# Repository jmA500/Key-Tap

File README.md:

# Key-Tap

This little gadget can listen to the keyboard of an Amiga 500 and catch
certain hotkeys. These hotkeys can be used to drive output pins that can 
configure internal extentions. 

Please have a look at the project website:

https://www.jm27.de/key-tap-a-hardware-configurator-for-the-amiga-500/

# License

	All material is freely usable under the GPL v2

# Directory structure

	* hardware: Contains Eagle PCB files
	* firmware: Pre-built hex-files for different MCUs
	* src: the C-source code
	* doc: Documentation

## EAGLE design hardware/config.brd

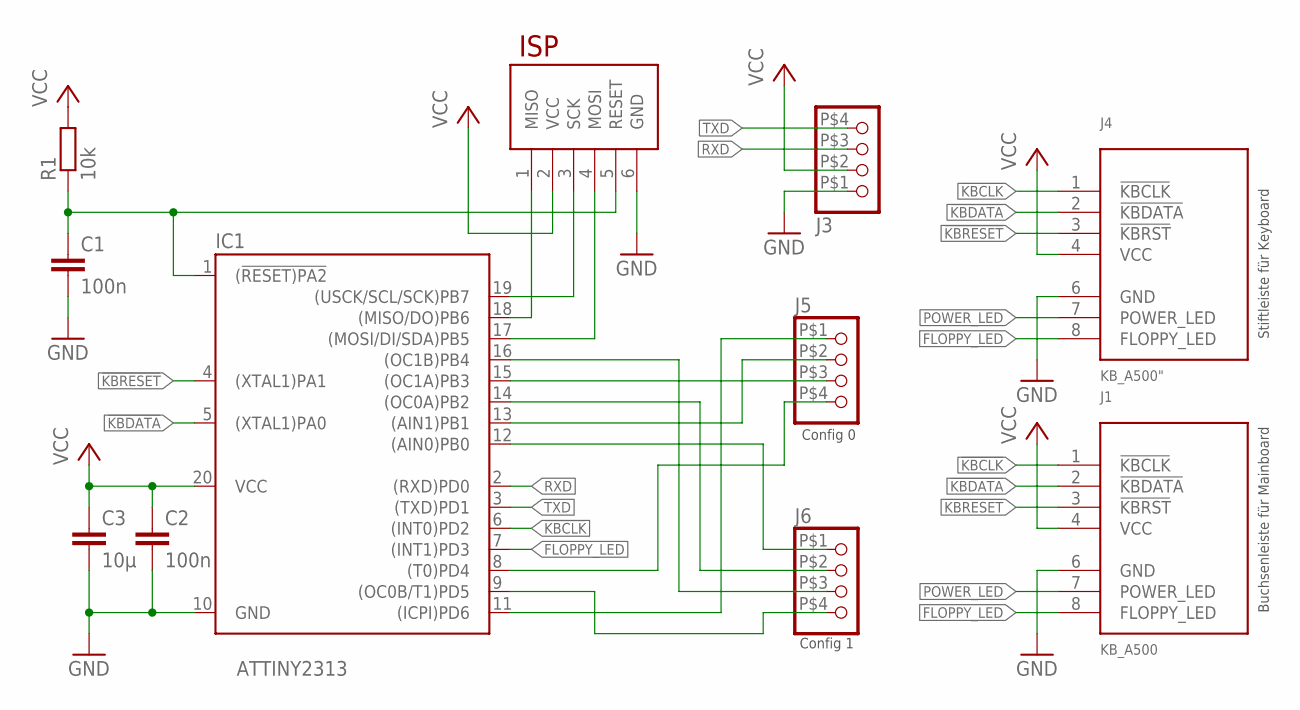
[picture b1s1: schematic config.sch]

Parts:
C1, C2: 100n; C0805
C3: 10µ; C1206
IC1: ATTINY2313; SO20L
J1: KB_A500; 1X08S
J2: ISP; 2X03
J3, J5, J6: PINHD-1X4; 1X04SLIM
J4: KB_A500"; 1X08/90SLIM
R1: 10k; R0805

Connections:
!KBCLK: IC1.6 ((INT0)PD2), J1.1 (!KBCLK), J4.1 (!KBCLK)
!KBDATA: IC1.5 ((XTAL1)PA0), J1.2 (!KBDATA), J4.2 (!KBDATA)
!KBRESET: IC1.4 ((XTAL1)PA1), J1.3 (!KBRST), J4.3 (!KBRST)
FLOPPY_LED: IC1.7 ((INT1)PD3), J1.8 (FLOPPY_LED), J4.8 (FLOPPY_LED)
GND: C1.2, C2.2, C3.2, IC1.10 (GND), J1.6 (GND), J2.6 (GND), J3.P$1 (1), J4.6 (GND)
MISO: IC1.18 ((MISO/DO)PB6), J2.1 (MISO)
MOSI: IC1.17 ((MOSI/DI/SDA)PB5), J2.4 (MOSI)
unnamed: IC1.12 ((AIN0)PB0), J6.P$1 (1)
unnamed: IC1.9 ((OC0B/T1)PD5), J6.P$4 (4)
unnamed: C1.1, IC1.1 ((!RESET)PA2), J2.5 (RESET), R1.1
PB1: IC1.13 ((AIN1)PB1), J5.P$2 (2)
PB2: IC1.14 ((OC0A)PB2), J6.P$2 (2)
PB3: IC1.15 ((OC1A)PB3), J5.P$3 (3)
PB4: IC1.16 ((OC1B)PB4), J6.P$3 (3)
PD4: IC1.8 ((T0)PD4), J5.P$4 (4)
PD6: IC1.11 ((ICPI)PD6), J5.P$1 (1)
POWER_LED: J1.7 (POWER_LED), J4.7 (POWER_LED)
RXD: IC1.2 ((RXD)PD0), J3.P$3 (3)
SCK: IC1.19 ((USCK/SCL/SCK)PB7), J2.3 (SCK)
TXD: IC1.3 ((TXD)PD1), J3.P$4 (4)
VCC: C2.1, C3.1, IC1.20 (VCC), J1.4 (VCC), J2.2 (VCC), J3.P$2 (2), J4.4 (VCC), R1.2

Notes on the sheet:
Config 0
Config 1
Buchsenleiste für Mainboard
Stiftleiste für Keyboard

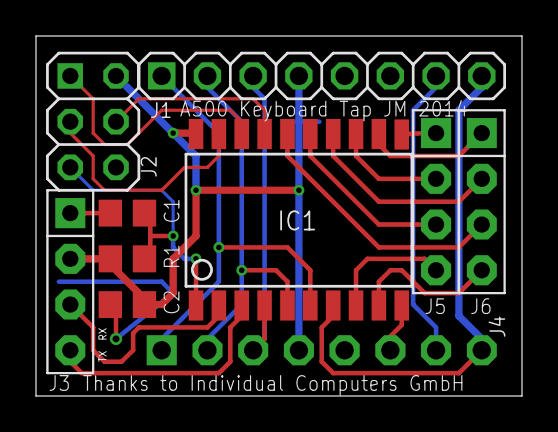
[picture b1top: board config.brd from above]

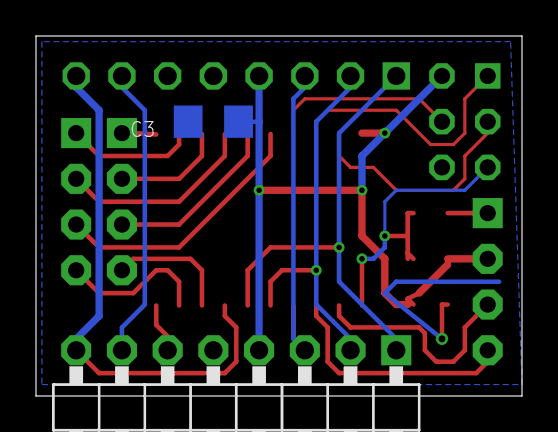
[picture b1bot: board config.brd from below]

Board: 2 copper layers, 27.0 x 20.0 mm, 11 parts (2 on the bottom side), 21 nets.

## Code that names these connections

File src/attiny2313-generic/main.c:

/************************************************************************
Title:    Main file for the firmware of an Amiga 500 Configurator. 
          Listens to the keyboard and takes keypresses to configure the 
          Amiga via some pins of the MCU.

Author:   Jan Metzger <jm@metweb.de>

License:  GNU General Public License 

LICENSE:
    Copyright (C) 2014-2017 Jan Metzger

    This program is free software; you can redistribute it and/or modify
    it under the terms of the GNU General Public License as published by
    the Free Software Foundation; either version 2 of the License, or
    any later version.

    This program is distributed in the hope that it will be useful,
    but WITHOUT ANY WARRANTY; without even the implied warranty of
    MERCHANTABILITY or FITNESS FOR A PARTICULAR PURPOSE.  See the
    GNU General Public License for more details.
    
************************************************************************/

#include <avr/io.h>
#include <avr/interrupt.h>
#include <avr/pgmspace.h>
#include <avr/eeprom.h>
#include <stdint.h>
#include <stdio.h>
#include <string.h>
#include <util/delay.h>
#include <ctype.h>
#include "key_tap.h"
#include "util.h"
#include "uart.h"
#include "uart_helper.h"
#include "ee_helper.h"

#define UART_DEBUG

#define CONFIG_PORT0 PORTD
#define CONFIG_DDR0  DDRD
#define CONFIG_BIT0  PD6

#define CONFIG_PORT1 PORTB
#define CONFIG_DDR1  DDRB
#define CONFIG_BIT1  PB1
 
#define CONFIG_PORT2 PORTB
#define CONFIG_DDR2  DDRB
#define CONFIG_BIT2  PB3 

#define CONFIG_PORT3 PORTD
#define CONFIG_DDR3  DDRD
#define CONFIG_BIT3  PD4 

#define CONFIG_PORT4 PORTB
#define CONFIG_DDR4  DDRB
#define CONFIG_BIT4  PB0
 
#define CONFIG_PORT5 PORTB
#define CONFIG_DDR5  DDRB
#define CONFIG_BIT5  PB2 
 
#define CONFIG_PORT6 PORTB
#define CONFIG_DDR6  DDRB
#define CONFIG_BIT6  PB4

#define CONFIG_PORT7 PORTD
#define CONFIG_DDR7  DDRD
#define CONFIG_BIT7  PD5

#define SET_BIT_TRI(PORT,DDR,BIT,STATE) { \
    if (STATE) \
      { (PORT) &= ~(1<<(BIT)); (DDR) |= (1<<(BIT)); } \
    else \
      { (DDR) &= ~(1<<(BIT)); } }

/* 
   The following variables store the current config. 
   Every bit corresponds to a config pin.
   Note that the interpretation is 'negative logic':
     1 means that the pin is pulled low (i.e. jumper on)
     0 means that the pin is high-z (i.e. jumper off)
*/

static struct
{
  uint8_t current;
  uint8_t next;
} conf;

void set_config()
{
  ee_save_config(conf.next);
  conf.current = conf.next;
  SET_BIT_TRI(CONFIG_PORT0, CONFIG_DDR0, CONFIG_BIT0, conf.current & (1<<0));
  SET_BIT_TRI(CONFIG_PORT1, CONFIG_DDR1, CONFIG_BIT1, conf.current & (1<<1));
  SET_BIT_TRI(CONFIG_PORT2, CONFIG_DDR2, CONFIG_BIT2, conf.current & (1<<2));
  SET_BIT_TRI(CONFIG_PORT3, CONFIG_DDR3, CONFIG_BIT3, conf.current & (1<<3));
  SET_BIT_TRI(CONFIG_PORT4, CONFIG_DDR4, CONFIG_BIT4, conf.current & (1<<4));
  SET_BIT_TRI(CONFIG_PORT5, CONFIG_DDR5, CONFIG_BIT5, conf.current & (1<<5));
  SET_BIT_TRI(CONFIG_PORT6, CONFIG_DDR6, CONFIG_BIT6, conf.current & (1<<6));
  SET_BIT_TRI(CONFIG_PORT7, CONFIG_DDR7, CONFIG_BIT7, conf.current & (1<<7));

#ifdef UART_DEBUG  
  while (uart_tx_char_present());
  uart_puts_P("CFG Load");
  uart_put_hex(conf.current);
  uart_put_newline();
#endif

  delay_ms(500);
}

inline void init()
{
  sei();
#ifdef UART_DEBUG  
  uart_init();
  uart_puts_P("KEYTAP Generic v1.0 JM 2017\n");
#endif
  kbd_init();
}

void uart_print_next()
{
#ifdef UART_DEBUG
  while (uart_tx_char_present());
  uart_puts_P("CFG next");
  uart_put_hex(conf.next);
  uart_put_newline();
#endif
}

void uart_print_current()
{
#ifdef UART_DEBUG
  while (uart_tx_char_present());
  uart_puts_P("CFG now");
  uart_put_hex(conf.current);
  uart_put_newline();
#endif
}

inline void uart_print_help()
{
#ifdef UART_DEBUG
  while (uart_tx_char_present());
  uart_puts_P("Commands\n?: Show\nh: help\n");
  while (uart_tx_char_present());
  uart_puts_P("! xx : Set config to hex value xx \n");
  while (uart_tx_char_present());
  uart_puts_P("res: reset\n");
#endif
}

inline void uart_print_err()
{
#ifdef UART_DEBUG
  while (uart_tx_char_present());
  uart_puts_P("Error\n");
#endif
}

inline void uart_print_fkey(uint8_t lastfkey)
{
#ifdef UART_DEBUG
  while (uart_tx_char_present());
  uart_puts_P("KEY reg F");
  uart_put_hex(lastfkey);
  uart_put_newline();
#endif
}

/* Parse input from UART. Format is simple but rigid, see uart_print_help() */
void parse (char* str)
{
  switch (str[0])
    {
    case '?':
      uart_print_next();
      uart_print_current();
      break;
    case 'h':
      uart_print_help();
      break;
    case '!':
      {
	uint8_t pos = 1;
	uint8_t resa,resb;

	while (str[pos]==' ')
	  { pos++; }

	resa = hexctoi(str[pos]);
	if (resa != 255)
	  {
	    resb = hexctoi(str[pos+1]);
	    if (resb != 255)
	      {
		conf.next = (resa<<4) + resb;
		uart_print_next();
	      }
	    else
	      {
		uart_print_err();
	      }
	  }
	else
	  {
	    uart_print_err();
	  }
      }
      break;
    case 'r':
      if ((str[1] == 'e') && (str[2] == 's'))
	{
	  kbd_do_reset();
	  set_config();
	  kbd_do_reset();
	}
      break;
    }
}

#define UARTBUF 16
void check_uart()
{
#ifdef UART_DEBUG
  static char buf[UARTBUF];
  static uint8_t bufpos = 0;

  if (uart_rx_char_present())
    {
      char res = uart_getc();
      switch (res)
	{
	case '\r':
	case '\n':
	  buf[bufpos] = 0;
	  parse(buf);
	  bufpos = 0;
	  break;
	case '\b':
	  if (bufpos)
	    bufpos--;
	  break;
	default:
	  if (bufpos < UARTBUF - 1)
	    {
	      buf[bufpos] = res;
	      bufpos++;
	    }
	}
    }
#endif 
}

int __attribute__((OS_main))
main()
{
  init();
  conf.next = ee_load_config();
  set_config();

  uint8_t res;
  uint8_t lastfkey = 0;
  uint8_t help_cnt = 0;
  uint8_t del_cnt = 0;
  uint8_t shift_flag = 0;

  for (;;)
    {
      check_uart();

      if (kbd_get_key(&res))
	{
	  /* The keycode is in the upper seven bits, push/release in the LSB, 
	     LSB = 0 if key is pressed, LSB = 1 if released*/
	  uint8_t code = res >> 1;
	  uint8_t push = (~res & 0x01);

	  /* This is the code that decides what to do if a keypress is detected.
	     Note that it also keeps track whether shift is active or not */
	  if (push)
	    {
	      if (code == KEY_HELP)
		{
		  help_cnt++;
		  if (help_cnt == 3)
		    {
		      if (lastfkey)
			{
			  uint8_t next = conf.next;
			  if ( (0 < lastfkey) && (lastfkey <= 8) )
			    {
			      next |= (1 << (lastfkey-1));
			    }
			  else if ( (11 <= lastfkey) && (lastfkey <= 18))
			    {
			      next &= ~(1 << (lastfkey - 11));
			    }
			  conf.next = next;
			  uart_print_next();
			}
		      else
			{
			  uart_puts_P("CFG no F before help\n");
			}
		    }
		}
	      else
		{
		  help_cnt = 0;
		  lastfkey = 0;
		}

	      if (code == KEY_DELETE)
		{
		  del_cnt++;
		  if (del_cnt == 3)
		    {
		      uart_print_current();
		      uart_print_next();
		    }
		}
	      else
		{
		  del_cnt = 0;
		}

	      if ((KEY_F1 <= code) & (code <= KEY_F10))
		{
		  lastfkey = code - KEY_F1 +1;
		  if (shift_flag)
		    lastfkey += 10;
		  uart_print_fkey(lastfkey);
		}

	      if ((code == KEY_SHIFTL) || (code == KEY_SHIFTR))
		{
		  shift_flag = 1;
		}
	    }
	  else
	    {
	      if ((code == KEY_SHIFTL) || (code==KEY_SHIFTR))
		{
		  shift_flag = 0;
		}
	    }
	}

      if (kbd_got_reset())
      	{
      	  set_config();
      	}
      
      if (kbd_got_long_reset())
	{
	  conf.next = CONFIG_DEFAULT;
      	  set_config();
	}
    }

  return 0;
}

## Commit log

2021-03-13 Initil import
2021-03-13 Typo corrected
2021-03-25 * Added a new function to the generic version:
    To configure an RGBtoHDMI Adapter one needs to emulate short and long
    pushes to a push button. This is done on the last Config Pin (JP6 / pin 4)
    when Pushing F9 (short) or F10 (long) while Holding HELP.
    Caveat: UART debugging is untested
2021-03-25 Added firmware files.
2021-03-25 * Added new PCB version with Atmega88
2021-03-25 * Removed an old testing version of the source code * Source for new Atmega88 version will be added later
2021-03-26 * Added two solder Jumpers for Hardware configurability * Increased length of PCB tomake it sit on the DSUb connector in the back of an A500
2021-03-29 * Makefile: Deleted -y Flag for avrdude * main.c: Changed Timing for long press * uart4313.c: Used wrong buffer size
